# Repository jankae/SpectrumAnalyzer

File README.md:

# SpectrumAnalyzer
It started as some general experiments with RF stuff and gradually evolved into a (severely limited) spectrum analyzer. 

The main work is in the RF boards, consisting of various mixers, filters and amplifiers. Everything is controlled with an STM32F7 Nucleo board. As the MCU is not quite powerful enough to handle the digitized final IF (14bit@25MHz) it is supported by a Spartan6 FPGA (actually, the STM is fast enough to *sample* the ADC but not fast enough to calculate the FFT on the fly and lacks the memory to store all samples for a later calculation).

Originally, the plan was to add a display, some buttons and a case and actually use it as a home-built spectrum analyzer. Ironically I had to buy a spectrum analyzer to solve some problems while building this setup. Now that I have a SSA3021X sitting on the bench, I don't think I can come up with the motiviation to finish this thing. It does work, it is just not very usable (e.g. hard coded values for span, resolution bandwidth,...)

Frequency plan:

* Input: 5MHz-1.8GHz
* 1.IF: 2.15GHz
* 2.IF: 403MHz
* 3.IF: 18.75MHz

And some measurements (no calibration done, so amplitude is off by a few db):

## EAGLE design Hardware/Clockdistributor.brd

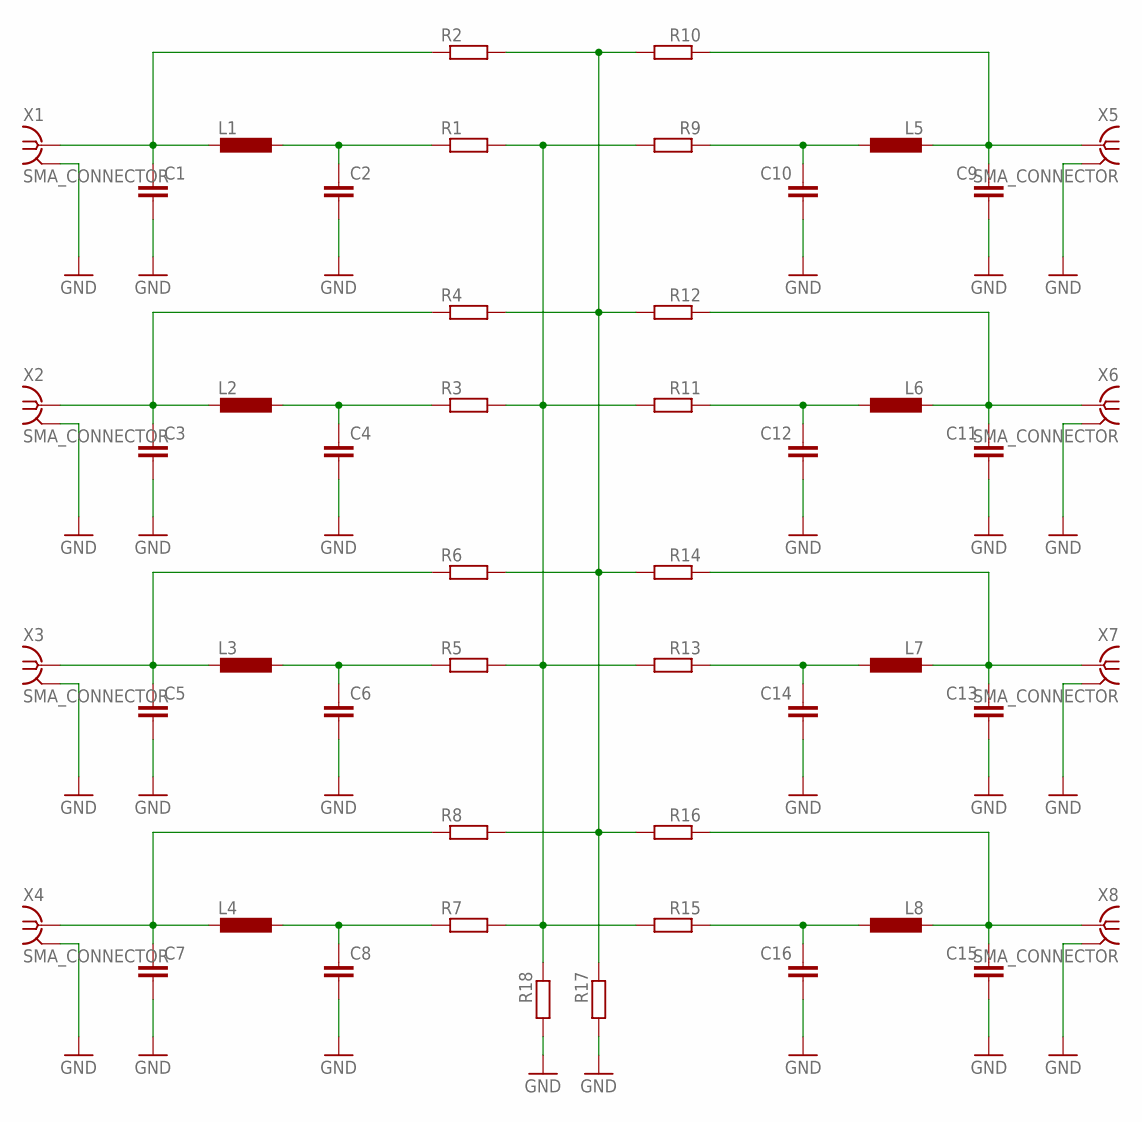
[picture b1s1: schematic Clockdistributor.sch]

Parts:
C1, C2, C3, C4, C5, C6, C7, C8, C9, C10, C11, C12, C13, C14, C15, C16: C-EUC0603; C0603
L1, L2, L3, L4, L5, L6, L7, L8: L-EUL2012C; L2012C
R1, R2, R3, R4, R5, R6, R7, R8, R9, R10, R11, R12, R13, R14, R15, R16, R17, R18: R-EU_R0603; R0603
X1, X2, X3, X4, X5, X6, X7, X8: SMA_CONNECTOR; J502-ND-142-0711-821/826

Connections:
GND: C1.2, C2.2, C3.2, C4.2, C5.2, C6.2, C7.2, C8.2, C9.2, C10.2, C11.2, C12.2, C13.2, C14.2, C15.2, C16.2, R17.2, R18.2, X1.G@1 (2), X1.G@2 (2), X1.G@3 (2), X1.G@4 (2), X2.G@1 (2), X2.G@2 (2), X2.G@3 (2), X2.G@4 (2), X3.G@1 (2), X3.G@2 (2), X3.G@3 (2), X3.G@4 (2), X4.G@1 (2), X4.G@2 (2), X4.G@3 (2), X4.G@4 (2), X5.G@1 (2), X5.G@2 (2), X5.G@3 (2), X5.G@4 (2), X6.G@1 (2), X6.G@2 (2), X6.G@3 (2), X6.G@4 (2), X7.G@1 (2), X7.G@2 (2), X7.G@3 (2), X7.G@4 (2), X8.G@1 (2), X8.G@2 (2), X8.G@3 (2), X8.G@4 (2)
unnamed: C1.1, L1.2, R2.1, X1.1
unnamed: C2.1, L1.1, R1.1
unnamed: C3.1, L2.2, R4.1, X2.1
unnamed: C4.1, L2.1, R3.1
unnamed: C5.1, L3.2, R6.1, X3.1
unnamed: C6.1, L3.1, R5.1
unnamed: C7.1, L4.2, R8.1, X4.1
unnamed: C8.1, L4.1, R7.1
unnamed: C9.1, L5.2, R10.1, X5.1
unnamed: C10.1, L5.1, R9.1
unnamed: C11.1, L6.2, R12.1, X6.1
unnamed: C12.1, L6.1, R11.1
unnamed: C13.1, L7.2, R14.1, X7.1
unnamed: C14.1, L7.1, R13.1
unnamed: C15.1, L8.2, R16.1, X8.1
unnamed: C16.1, L8.1, R15.1
unnamed: R2.2, R4.2, R6.2, R8.2, R10.2, R12.2, R14.2, R16.2, R17.1
unnamed: R1.2, R3.2, R5.2, R7.2, R9.2, R11.2, R13.2, R15.2, R18.1

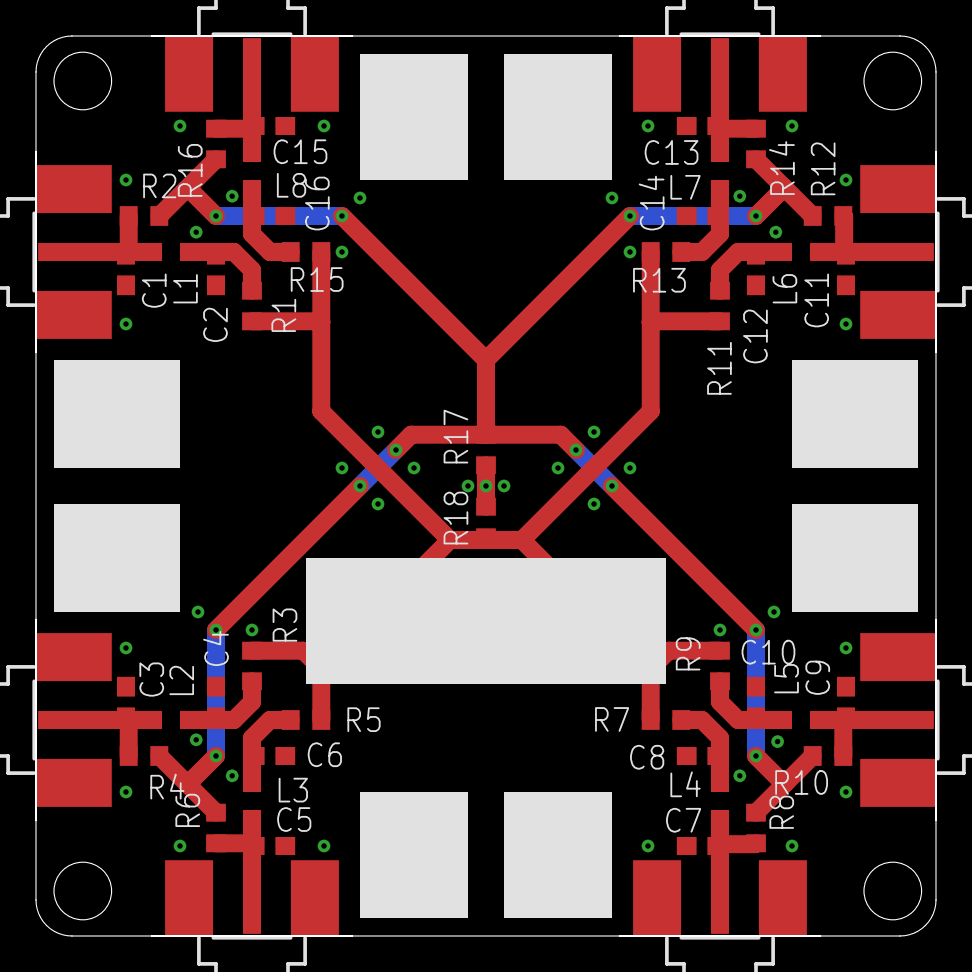
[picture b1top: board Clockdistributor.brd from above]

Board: 2 copper layers, 50.0 x 50.0 mm, 50 parts (0 on the bottom side), 19 nets.

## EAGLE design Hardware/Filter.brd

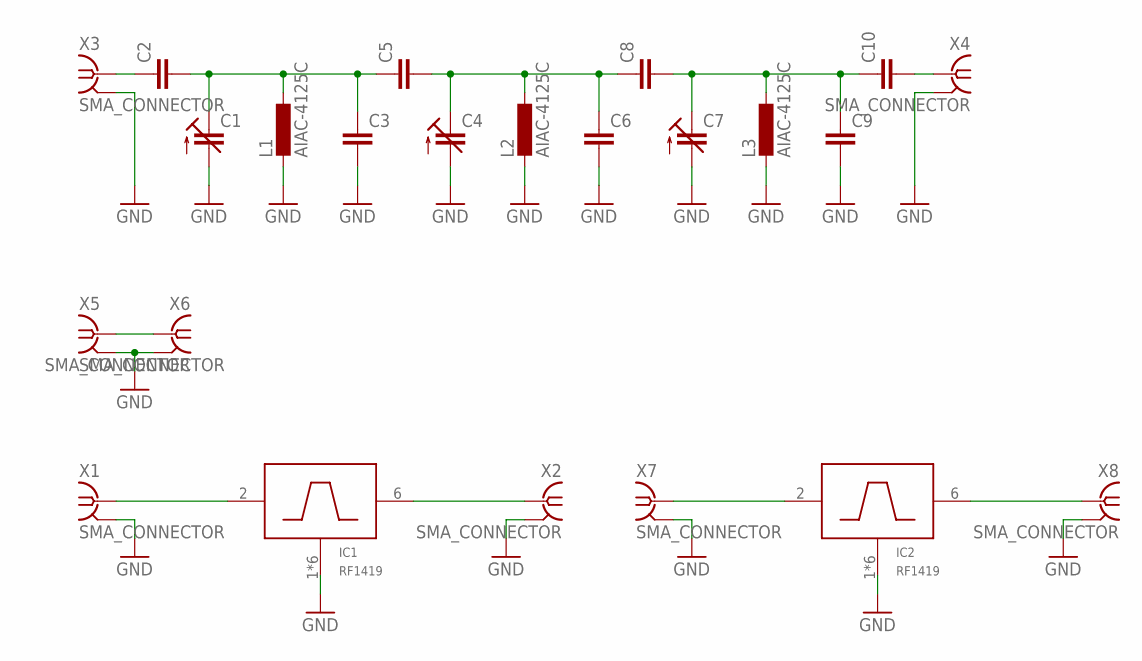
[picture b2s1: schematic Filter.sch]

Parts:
C1, C4, C7: C-TRIMMCTZ3; CTRIMCTZ3
C2, C3, C5, C6, C8, C9, C10: C-EUC0603; C0603
IC1, IC2: RF1419; RESCAV127P380X380X120-8
L1, L2, L3: AIAC-4125C
X1, X2, X3, X4, X5, X6, X7, X8: SMA_CONNECTOR; J502-ND-142-0711-821/826

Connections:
GND: C1.2 (A), C3.2, C4.2 (A), C6.2, C7.2 (A), C9.2, IC1.1 (GND), IC1.3 (GND), IC1.4 (GND), IC1.5 (GND), IC1.7 (GND), IC1.8 (GND), IC2.1 (GND), IC2.3 (GND), IC2.4 (GND), IC2.5 (GND), IC2.7 (GND), IC2.8 (GND), L1.P$2 (2), L2.P$2 (2), L3.P$2 (2), X1.G@1 (2), X1.G@2 (2), X1.G@3 (2), X1.G@4 (2), X2.G@1 (2), X2.G@2 (2), X2.G@3 (2), X2.G@4 (2), X3.G@1 (2), X3.G@2 (2), X3.G@3 (2), X3.G@4 (2), X4.G@1 (2), X4.G@2 (2), X4.G@3 (2), X4.G@4 (2), X5.G@1 (2), X5.G@2 (2), X5.G@3 (2), X5.G@4 (2), X6.G@1 (2), X6.G@2 (2), X6.G@3 (2), X6.G@4 (2), X7.G@1 (2), X7.G@2 (2), X7.G@3 (2), X7.G@4 (2), X8.G@1 (2), X8.G@2 (2), X8.G@3 (2), X8.G@4 (2)
unnamed: C2.1, X3.1
unnamed: IC1.2 (IN), X1.1
unnamed: IC1.6 (OUT), X2.1
unnamed: C1.1 (E), C2.2, C3.1, C5.1, L1.P$1 (1)
unnamed: C4.1 (E), C5.2, C6.1, C8.1, L2.P$1 (1)
unnamed: C7.1 (E), C8.2, C9.1, C10.1, L3.P$1 (1)
unnamed: C10.2, X4.1
unnamed: X5.1, X6.1
unnamed: IC2.2 (IN), X7.1
unnamed: IC2.6 (OUT), X8.1

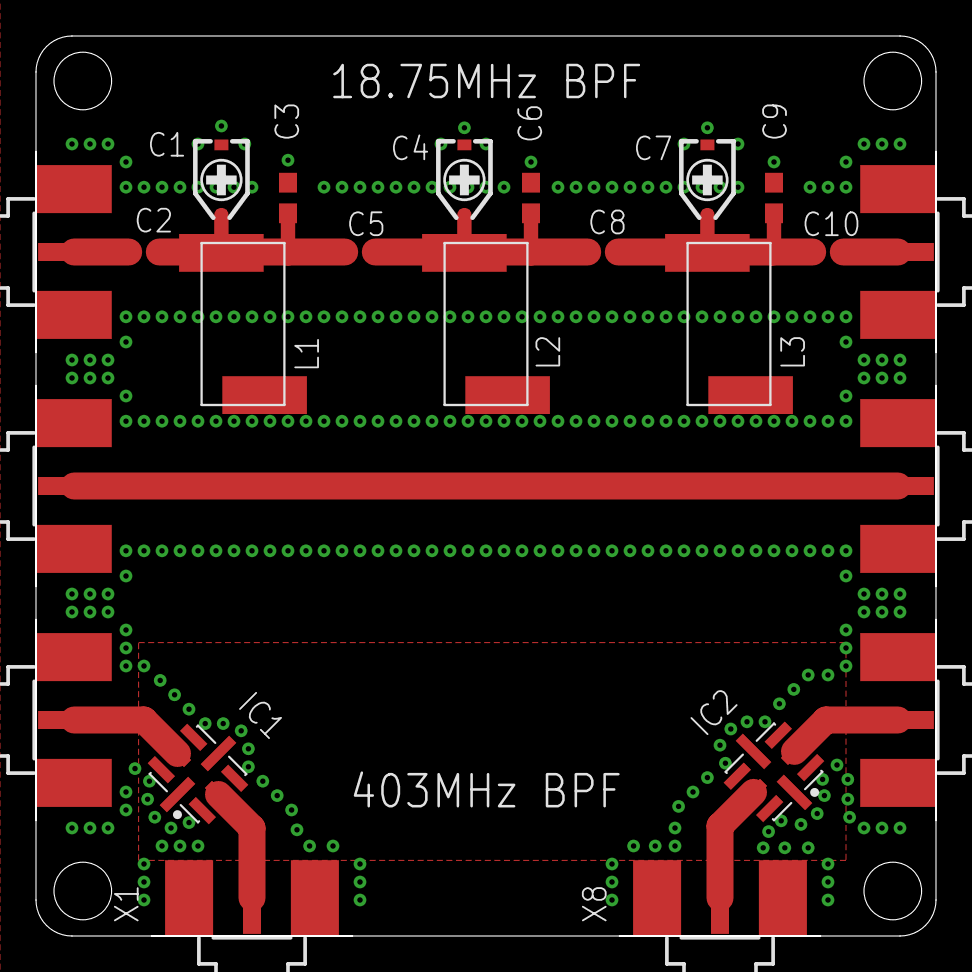
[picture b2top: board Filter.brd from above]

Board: 2 copper layers, 50.0 x 50.0 mm, 23 parts (0 on the bottom side), 11 nets.

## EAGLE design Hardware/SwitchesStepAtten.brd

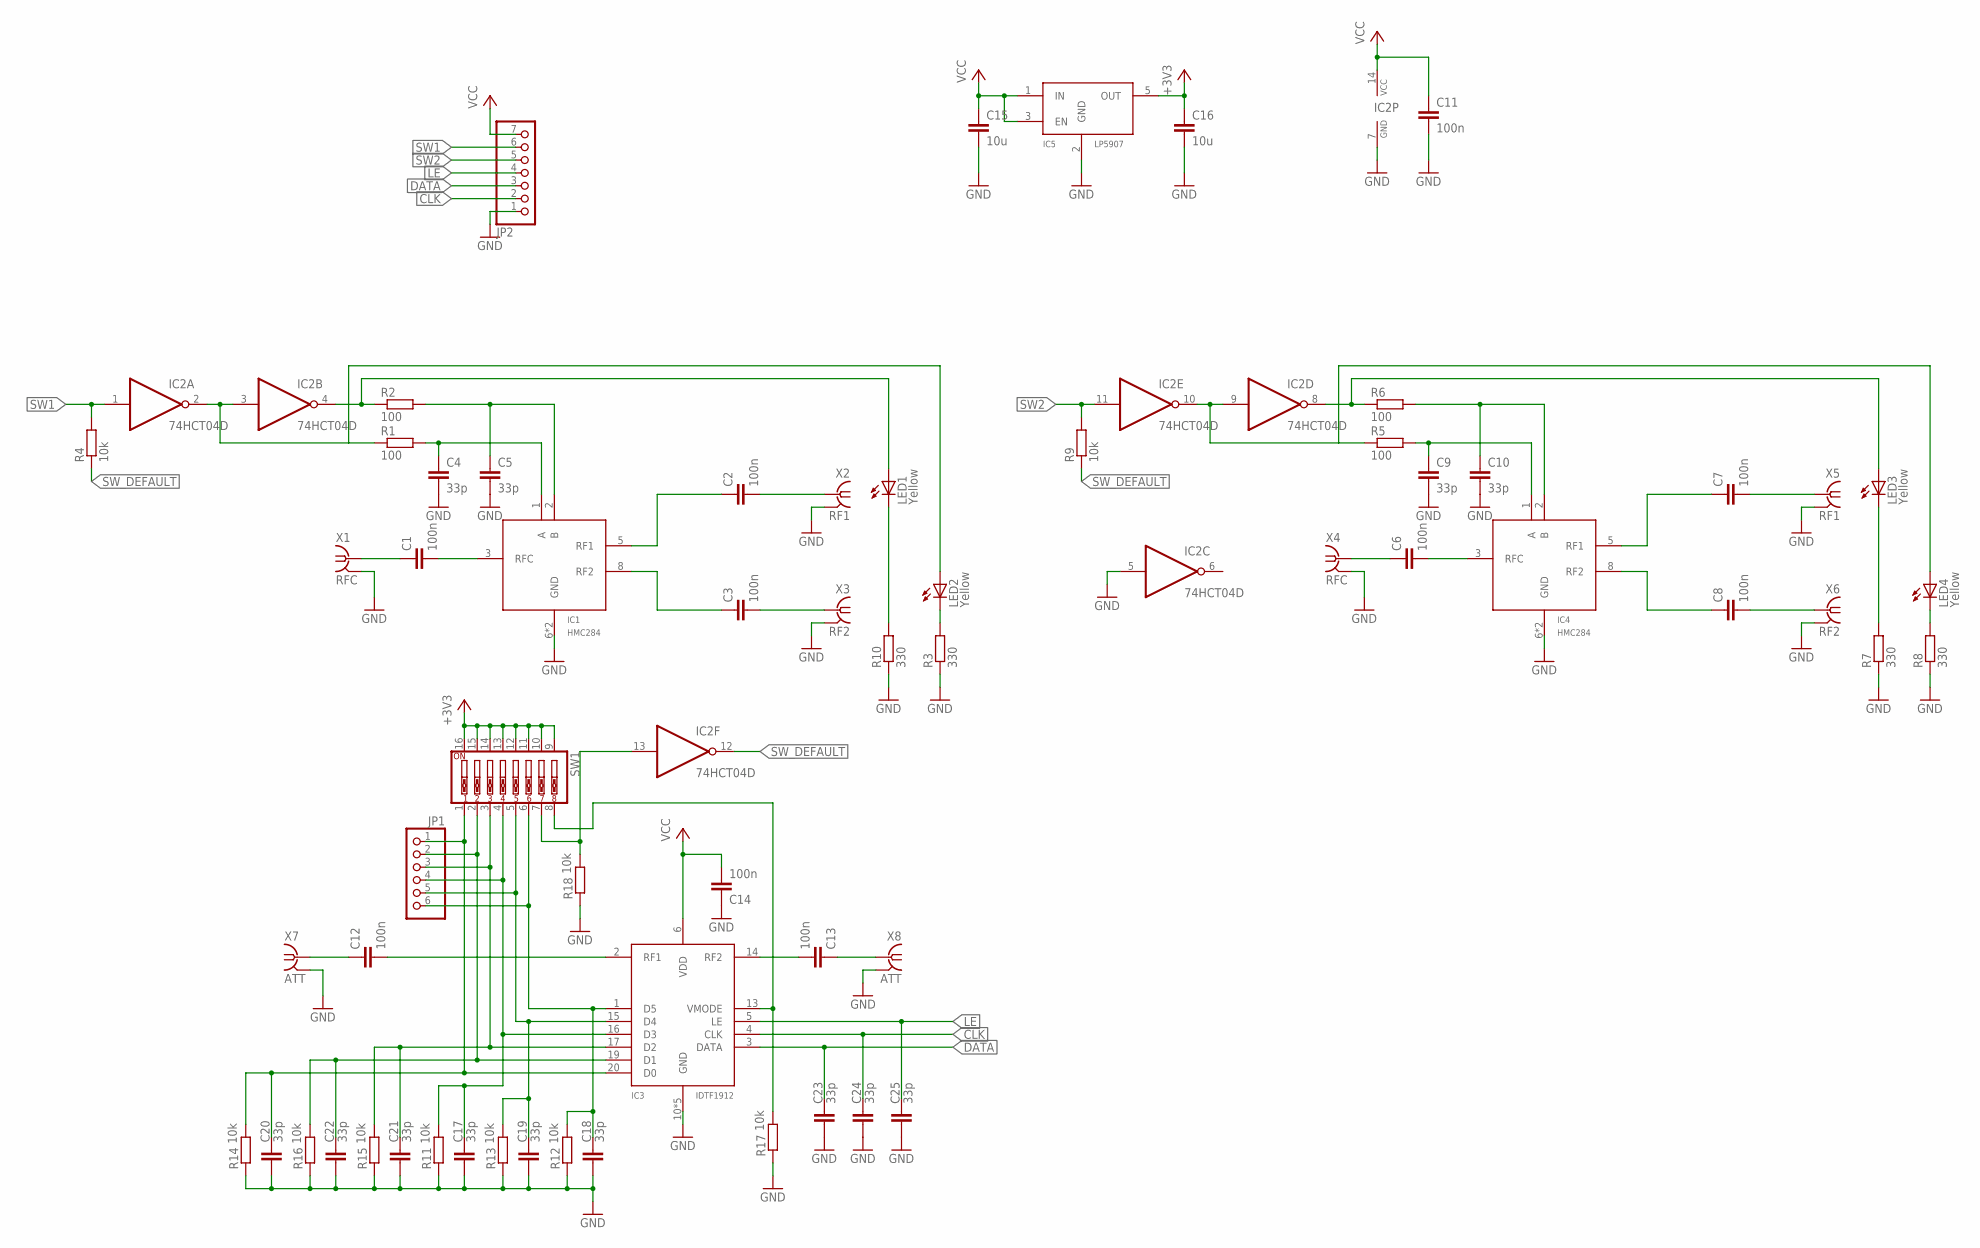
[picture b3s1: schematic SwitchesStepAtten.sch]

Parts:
C1, C2, C3, C6, C7, C8, C11, C12, C13, C14: 100n; C0603
C4, C5, C9, C10, C17, C18, C19, C20, C21, C22, C23, C24, C25: 33p; C0603
C15, C16: 10u; C1206K
IC1, IC4: HMC284; MSOP08
IC2: 74HCT04D; SO14
IC3: IDTF1912; QFN50P400X400X75-21T206
IC5: LP5907; SOT23-5L
JP1: PINHD-1X6; 1X06
JP2: PINHD-1X7/90; 1X07/90
LED1, LED2, LED3, LED4: Yellow; LED_SML0603
R1, R2, R5, R6: 100; R0603
R3, R7, R8, R10: 330; R0603
R4, R9, R11, R12, R13, R14, R15, R16, R17, R18: 10k; R0603
SW1: SW_DIP-8; EDG-08
X1, X4: RFC; J502-ND-142-0711-821/826
X2, X5: RF1; J502-ND-142-0711-821/826
X3, X6: RF2; J502-ND-142-0711-821/826
X7, X8: ATT; J502-ND-142-0711-821/826

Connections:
+3V3: C16.1, IC5.5 (OUT), SW1.9, SW1.10, SW1.11, SW1.12, SW1.13, SW1.14, SW1.15, SW1.16
CLK: C24.1, IC3.4 (CLK), JP2.2
DATA: C23.1, IC3.3 (DATA), JP2.3
GND: C4.2, C5.2, C9.2, C10.2, C11.2, C14.1, C15.2, C16.2, C17.2, C18.2, C19.2, C20.2, C21.2, C22.2, C23.2, C24.2, C25.2, IC1.6 (GND), IC1.7 (GND), IC2.5 (I), IC2.7 (GND), IC3.10 (GND), IC3.11 (GND), IC3.12 (GND), IC3.18 (GND), IC3.21 (GND), IC4.6 (GND), IC4.7 (GND), IC5.2 (GND), JP2.1, R3.1, R7.1, R8.1, R10.1, R11.1, R12.1, R13.1, R14.1, R15.1, R16.1, R17.1, R18.1, X1.G@1 (2), X1.G@2 (2), X1.G@3 (2), X1.G@4 (2), X2.G@1 (2), X2.G@2 (2), X2.G@3 (2), X2.G@4 (2), X3.G@1 (2), X3.G@2 (2), X3.G@3 (2), X3.G@4 (2), X4.G@1 (2), X4.G@2 (2), X4.G@3 (2), X4.G@4 (2), X5.G@1 (2), X5.G@2 (2), X5.G@3 (2), X5.G@4 (2), X6.G@1 (2), X6.G@2 (2), X6.G@3 (2), X6.G@4 (2), X7.G@1 (2), X7.G@2 (2), X7.G@3 (2), X7.G@4 (2), X8.G@1 (2), X8.G@2 (2), X8.G@3 (2), X8.G@4 (2)
LE: C25.1, IC3.5 (LE), JP2.4
unnamed: C5.1, IC1.2 (B), R2.2
unnamed: C4.1, IC1.1 (A), R1.2
unnamed: C1.1, X1.1
unnamed: C1.2, IC1.3 (RFC)
unnamed: C2.1, IC1.5 (RF1)
unnamed: C2.2, X2.1
unnamed: C3.1, IC1.8 (RF2)
unnamed: C3.2, X3.1
unnamed: IC2.4 (O), LED1.A, R2.1
unnamed: IC2.2 (O), IC2.3 (I), LED2.A, R1.1
unnamed: C10.1, IC4.2 (B), R6.2
unnamed: LED2.C, R3.2
unnamed: C9.1, IC4.1 (A), R5.2
unnamed: C6.1, X4.1
unnamed: C6.2, IC4.3 (RFC)
unnamed: C7.1, IC4.5 (RF1)
unnamed: C7.2, X5.1
unnamed: C8.1, IC4.8 (RF2)
unnamed: C8.2, X6.1
unnamed: IC2.8 (O), LED3.A, R6.1
unnamed: IC2.9 (I), IC2.10 (O), LED4.A, R5.1
unnamed: LED3.C, R7.2
unnamed: LED4.C, R8.2
unnamed: C12.1, X7.1
unnamed: C12.2, IC3.2 (RF1)
unnamed: C13.1, X8.1
unnamed: C13.2, IC3.14 (RF2)
unnamed: C20.1, IC3.20 (D0), JP1.1, R14.2, SW1.1
unnamed: LED1.C, R10.2
unnamed: C22.1, IC3.19 (D1), JP1.2, R16.2, SW1.2
unnamed: C21.1, IC3.17 (D2), JP1.3, R15.2, SW1.3
unnamed: IC2.13 (I), R18.2, SW1.7
unnamed: C19.1, IC3.15 (D4), JP1.5, R13.2, SW1.5
unnamed: IC3.13 (VMODE), R17.2, SW1.8
unnamed: C18.1, IC3.1 (D5), JP1.6, R12.2, SW1.6
unnamed: C17.1, IC3.16 (D3), JP1.4, R11.2, SW1.4
SW1: IC2.1 (I), JP2.6, R4.2
SW2: IC2.11 (I), JP2.5, R9.2
SW_DEFAULT: IC2.12 (O), R4.1, R9.1
VCC: C11.1, C14.2, C15.1, IC2.14 (VCC), IC3.6 (VDD), IC5.1 (IN), IC5.3 (EN), JP2.7

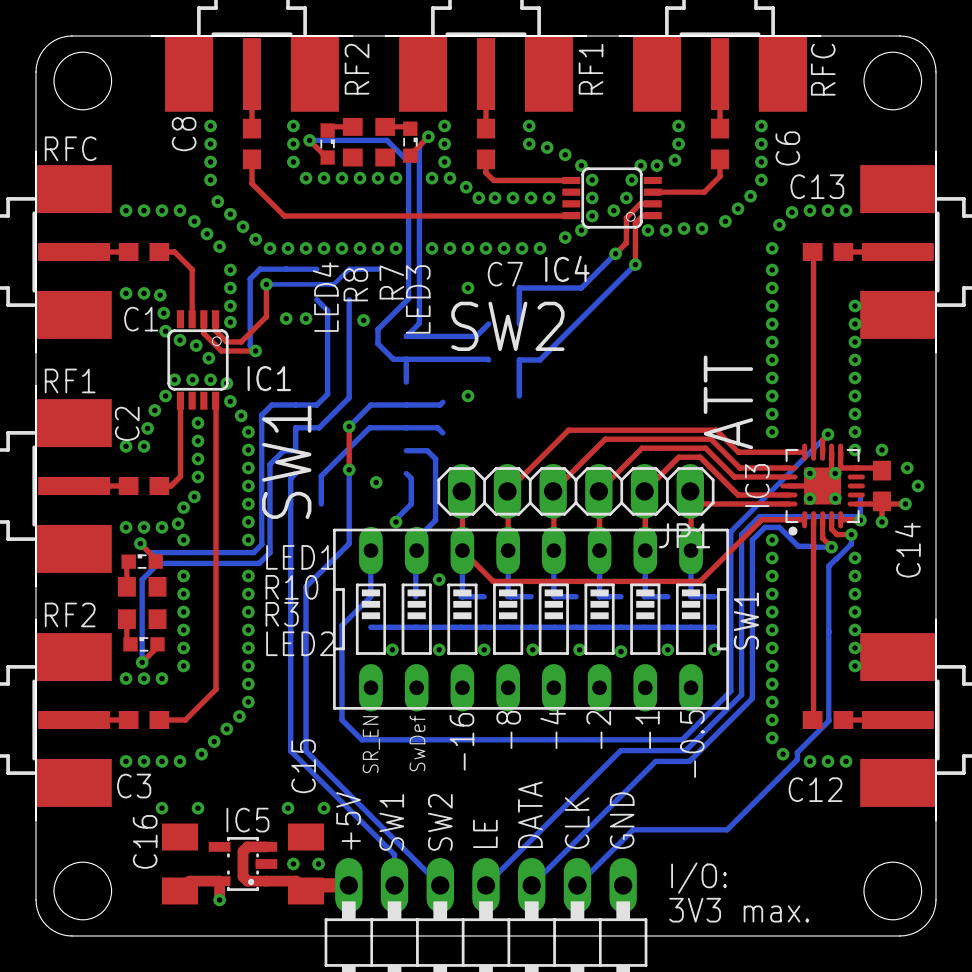
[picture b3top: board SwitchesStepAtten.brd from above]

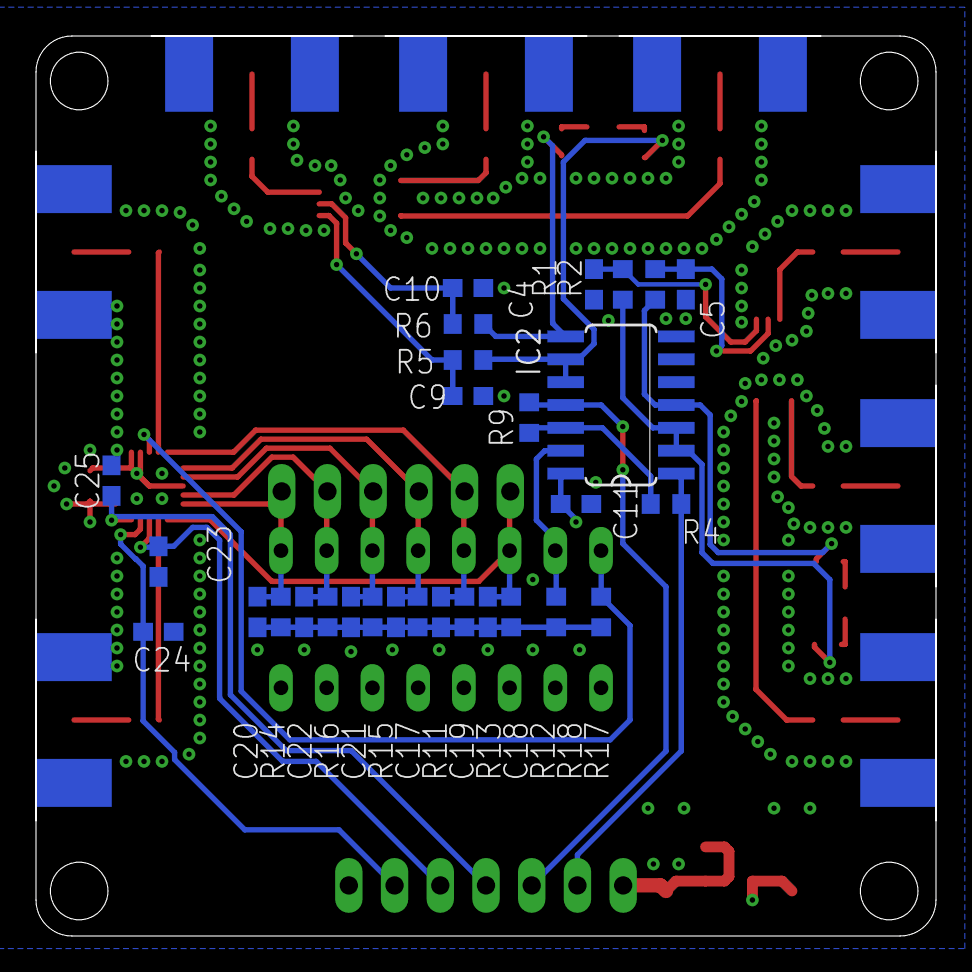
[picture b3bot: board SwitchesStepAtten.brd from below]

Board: 4 copper layers, 50.0 x 50.0 mm, 63 parts (29 on the bottom side), 45 nets.

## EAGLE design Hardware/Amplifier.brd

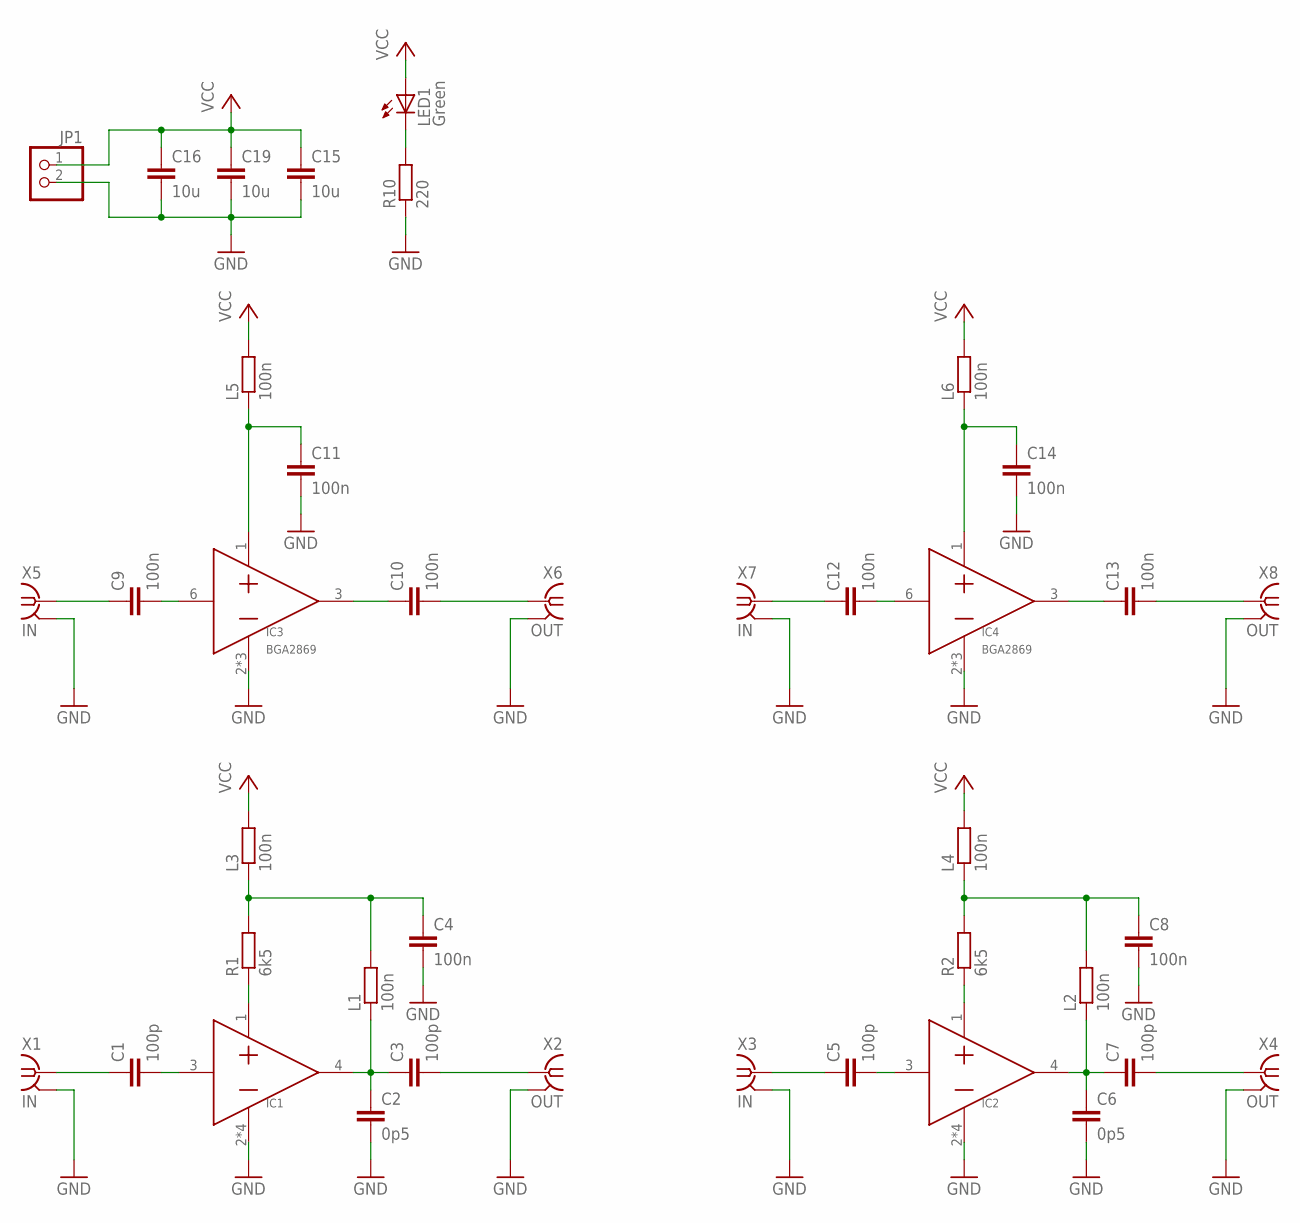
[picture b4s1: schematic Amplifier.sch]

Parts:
C1, C3, C5, C7: 100p; C0603
C2, C6: 0p5; C0603
C4, C8, C9, C10, C11, C12, C13, C14: 100n; C0603
C15, C16, C19: 10u; C1206
IC1, IC2: GRF4002; SON50P150X150X45-7T60X110
IC3, IC4: BGA2869; SOT363
JP1: PINHD-1X2/90; 1X02/90
L1, L2, L3, L4, L5, L6: 100n; R0603
LED1: Green; LED_SML0603
R1, R2: 6k5; R0603
R10: 220; R0603
X1, X3, X5, X7: IN; J502-ND-142-0711-821/826
X2, X4, X6, X8: OUT; J502-ND-142-0711-821/826

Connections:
GND: C2.2, C4.2, C6.2, C8.2, C11.2, C14.2, C15.2, C16.2, C19.2, IC1.2 (GND), IC1.5 (GND), IC1.6 (GND), IC1.7 (GND), IC2.2 (GND), IC2.5 (GND), IC2.6 (GND), IC2.7 (GND), IC3.2 (GND), IC3.4 (GND), IC3.5 (GND), IC4.2 (GND), IC4.4 (GND), IC4.5 (GND), JP1.2, R10.1, X1.G@1 (2), X1.G@2 (2), X1.G@3 (2), X1.G@4 (2), X2.G@1 (2), X2.G@2 (2), X2.G@3 (2), X2.G@4 (2), X3.G@1 (2), X3.G@2 (2), X3.G@3 (2), X3.G@4 (2), X4.G@1 (2), X4.G@2 (2), X4.G@3 (2), X4.G@4 (2), X5.G@1 (2), X5.G@2 (2), X5.G@3 (2), X5.G@4 (2), X6.G@1 (2), X6.G@2 (2), X6.G@3 (2), X6.G@4 (2), X7.G@1 (2), X7.G@2 (2), X7.G@3 (2), X7.G@4 (2), X8.G@1 (2), X8.G@2 (2), X8.G@3 (2), X8.G@4 (2)
unnamed: C1.1, X1.1
unnamed: C1.2, IC1.3 (IN)
unnamed: IC1.1 (VCC), R1.1
unnamed: C2.1, C3.1, IC1.4 (OUT), L1.1
unnamed: C3.2, X2.1
unnamed: C5.1, X3.1
unnamed: C5.2, IC2.3 (IN)
unnamed: IC2.1 (VCC), R2.1
unnamed: C6.1, C7.1, IC2.4 (OUT), L2.1
unnamed: C7.2, X4.1
unnamed: C9.1, X5.1
unnamed: C9.2, IC3.6 (IN)
unnamed: C12.1, X7.1
unnamed: C10.1, IC3.3 (OUT)
unnamed: C10.2, X6.1
unnamed: C12.2, IC4.6 (IN)
unnamed: C13.1, IC4.3 (OUT)
unnamed: C13.2, X8.1
unnamed: C4.1, L1.2, L3.1, R1.2
unnamed: C8.1, L2.2, L4.1, R2.2
unnamed: C11.1, IC3.1 (VCC), L5.1
unnamed: C14.1, IC4.1 (VCC), L6.1
unnamed: LED1.C, R10.2
VCC: C15.1, C16.1, C19.1, JP1.1, L3.2, L4.2, L5.2, L6.2, LED1.A

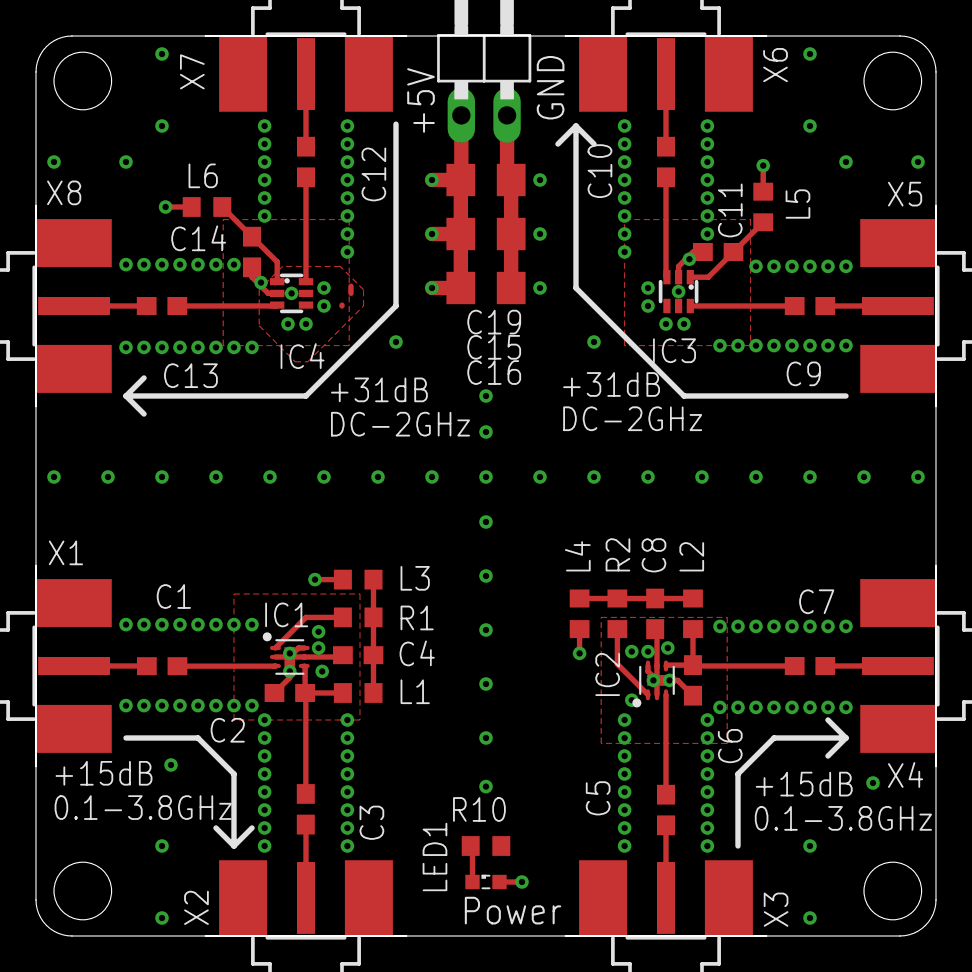
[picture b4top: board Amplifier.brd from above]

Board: 4 copper layers, 50.0 x 50.0 mm, 40 parts (0 on the bottom side), 25 nets.

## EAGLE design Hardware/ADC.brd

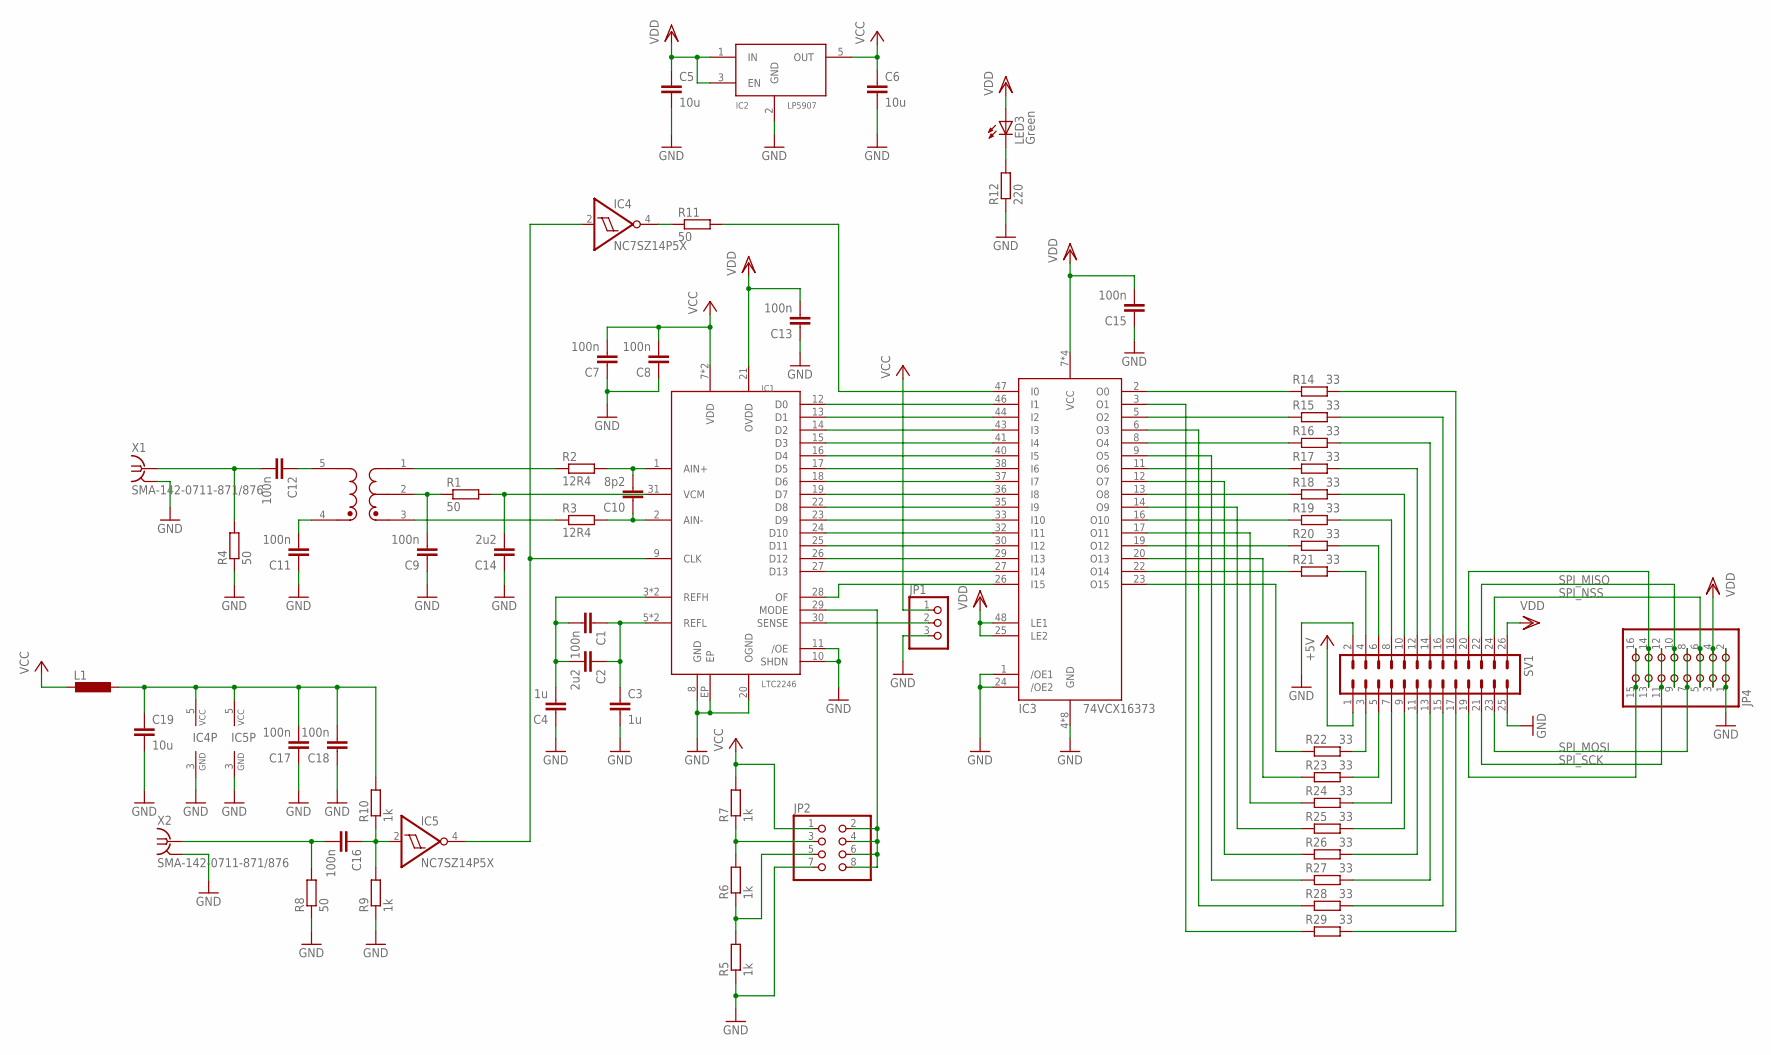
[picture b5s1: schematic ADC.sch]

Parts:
B1: ETC1-1T; SM-22
C1, C13: 100n; C0402K
C2, C14: 2u2; C0603K
C3, C4: 1u; C0603K
C5, C6, C19: 10u; C1206K
C7, C8, C9, C11, C12, C15, C16, C17, C18: 100n; C0603K
C10: 8p2; C0603K
IC1: LTC2246; TQFP32-EP
IC2: LP5907; SOT23-5L
IC3: 74VCX16373; SOP50P810X120-48
IC4, IC5: NC7SZ14P5X; SC70-5
JP1: PINHD-1X3; 1X03
JP2: PINHD-2X4; 2X04
JP4: PINHD-2X8/90; 2X08/90
L1: L-EUL2012C; L2012C
LED3: Green; LED_SML0603
R1, R4, R8, R11: 50; R0603
R2, R3: 12R4; R0603
R5, R6, R7, R9, R10: 1k; R0603
R12: 220; R0603
R14, R15, R16, R17, R18, R19, R20, R21, R22, R23, R24, R25, R26, R27, R28, R29: 33; R0603
SV1: ML26L
X1, X2: SMA-142-0711-871/876; J502-ND-142-0711-871/876

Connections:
+5V: SV1.1
GND: C3.2, C4.1, C5.2, C6.2, C7.1, C8.1, C9.1, C11.1, C13.1, C14.1, C15.1, C17.1, C18.1, C19.2, IC1.8 (GND), IC1.10 (SHDN), IC1.11 (/OE), IC1.20 (OGND), IC1.EP, IC2.2 (GND), IC3.1 (/OE1), IC3.4 (GND), IC3.10 (GND), IC3.15 (GND), IC3.21 (GND), IC3.24 (/OE2), IC3.28 (GND), IC3.34 (GND), IC3.39 (GND), IC3.45 (GND), IC4.3 (GND), IC5.3 (GND), JP1.3, JP2.7, JP4.1, JP4.2, R4.1, R5.1, R8.1, R9.1, R12.1, SV1.2, SV1.25, X1.G@1 (2), X1.G@2 (2), X1.G@3 (2), X1.G@4 (2), X2.G@1 (2), X2.G@2 (2), X2.G@3 (2), X2.G@4 (2)
unnamed: C1.1, C2.1, C3.1, IC1.5 (REFL), IC1.6 (REFL)
unnamed: C1.2, C2.2, C4.2, IC1.3 (REFH), IC1.4 (REFH)
unnamed: B1.2 (SEC_CT), C9.2, R1.1
unnamed: C14.2, IC1.31 (VCM), R1.2
unnamed: C10.2, IC1.1 (AIN+), R2.2
unnamed: B1.5 (PRI), C12.1
unnamed: C10.1, IC1.2 (AIN-), R3.2
unnamed: B1.3 (SEC_DOT), R3.1
unnamed: B1.4 (PRI_DOT), C11.2
unnamed: B1.1 (SEC), R2.1
unnamed: C12.2, R4.2, X1.1
unnamed: IC1.12 (D0), IC3.46 (I1)
unnamed: IC1.13 (D1), IC3.44 (I2)
unnamed: IC1.14 (D2), IC3.43 (I3)
unnamed: IC1.15 (D3), IC3.41 (I4)
unnamed: IC1.16 (D4), IC3.40 (I5)
unnamed: IC1.17 (D5), IC3.38 (I6)
unnamed: IC1.18 (D6), IC3.37 (I7)
unnamed: IC1.19 (D7), IC3.36 (I8)
unnamed: IC1.22 (D8), IC3.35 (I9)
unnamed: IC1.23 (D9), IC3.33 (I10)
unnamed: IC1.24 (D10), IC3.32 (I11)
unnamed: IC1.25 (D11), IC3.30 (I12)
unnamed: IC1.26 (D12), IC3.29 (I13)
unnamed: IC1.27 (D13), IC3.27 (I14)
unnamed: IC1.28 (OF), IC3.26 (I15)
unnamed: R18.2, SV1.10
unnamed: IC3.23 (O15), R22.1
unnamed: IC3.22 (O14), R21.1
unnamed: IC3.20 (O13), R23.1
unnamed: IC3.19 (O12), R20.1
unnamed: IC3.17 (O11), R24.1
unnamed: R19.2, SV1.8
unnamed: IC3.14 (O9), R25.1
unnamed: IC3.12 (O7), R26.1
unnamed: R17.2, SV1.12
unnamed: IC3.9 (O5), R27.1
unnamed: R16.2, SV1.14
unnamed: IC3.6 (O3), R28.1
unnamed: R15.2, SV1.16
unnamed: IC3.3 (O1), R29.1
unnamed: R14.2, SV1.18
unnamed: IC1.30 (SENSE), JP1.2
unnamed: JP2.5, R5.2, R6.1
unnamed: JP2.3, R6.2, R7.1
unnamed: IC1.29 (MODE), JP2.2, JP2.4, JP2.6, JP2.8
unnamed: C16.1, IC5.2 (I), R9.2, R10.1
unnamed: C16.2, R8.2, X2.1
unnamed: IC1.9 (CLK), IC4.2 (I), IC5.4 (O)
unnamed: IC4.4 (O), R11.1
unnamed: IC3.47 (I0), R11.2
unnamed: LED3.C, R12.2
unnamed: IC3.2 (O0), R14.1
unnamed: IC3.5 (O2), R15.1
unnamed: IC3.8 (O4), R16.1
unnamed: IC3.11 (O6), R17.1
unnamed: IC3.13 (O8), R18.1
unnamed: IC3.16 (O10), R19.1
unnamed: R20.2, SV1.6
unnamed: R21.2, SV1.4
unnamed: R22.2, SV1.3
unnamed: R23.2, SV1.5
unnamed: R24.2, SV1.7
unnamed: R25.2, SV1.9
unnamed: R26.2, SV1.11
unnamed: R27.2, SV1.13
unnamed: R28.2, SV1.15
unnamed: R29.2, SV1.17
unnamed: JP4.13, JP4.14, SV1.20
unnamed: JP4.15, JP4.16, SV1.19
SPI_MISO: JP4.9, JP4.10, SV1.22
SPI_MOSI: JP4.7, JP4.8, SV1.23
SPI_NSS: JP4.5, JP4.6, SV1.24
SPI_SCK: JP4.11, JP4.12, SV1.21
VCC: C6.1, C7.2, C8.2, IC1.7 (VDD), IC1.32 (VDD), IC2.5 (OUT), JP1.1, JP2.1, L1.2, R7.2
VCC1: C17.2, C18.2, C19.1, IC4.5 (VCC), IC5.5 (VCC), L1.1, R10.2
VDD: C5.1, C13.2, C15.2, IC1.21 (OVDD), IC2.1 (IN), IC2.3 (EN), IC3.7 (VCC), IC3.18 (VCC), IC3.25 (LE2), IC3.31 (VCC), IC3.42 (VCC), IC3.48 (LE1), JP4.3, JP4.4, LED3.A, SV1.26

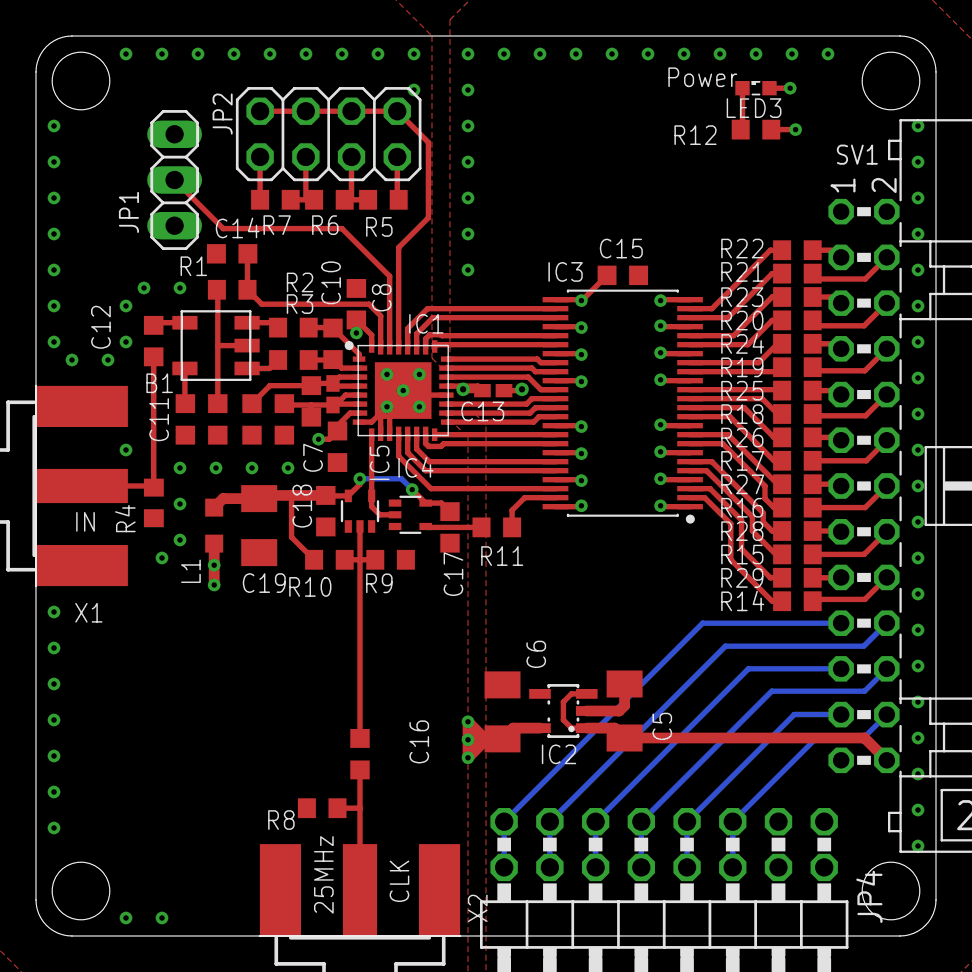
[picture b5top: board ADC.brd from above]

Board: 4 copper layers, 50.0 x 50.0 mm, 61 parts (0 on the bottom side), 78 nets.
